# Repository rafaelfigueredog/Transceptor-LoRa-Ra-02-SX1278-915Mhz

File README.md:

# Transceptor-LoRa-Ra-02-SX1278-915Mhz

Este projeto visa a criação de um Transceptor-LoRa-Ra-02-SX1278-915Mhz destinado a disciplina de Técnicas de Prototipagem do curso de Engenharia de Computação no Instituto Federal da Paraíba

## Grupo

  Allan Bispo <br />
  Lucas Mateus <br />
  Rafael Guimarães <br />
  
## Componentes

- Transceptor LoRa Ra-02 SX1278 915Mhz
- Microcontrolador ATmega328
- Bateria de 5v Li-ion

## Aplicação - Monitoramento de Animais. 

Esse projeto visa a criação de um dispositivo que emite sinais de radio frequencia, de modo que seja possível estimar a distância entre o animal e um ponto específico determinado pelo usuário do projeto auxiliando o dono a localizar o animal.

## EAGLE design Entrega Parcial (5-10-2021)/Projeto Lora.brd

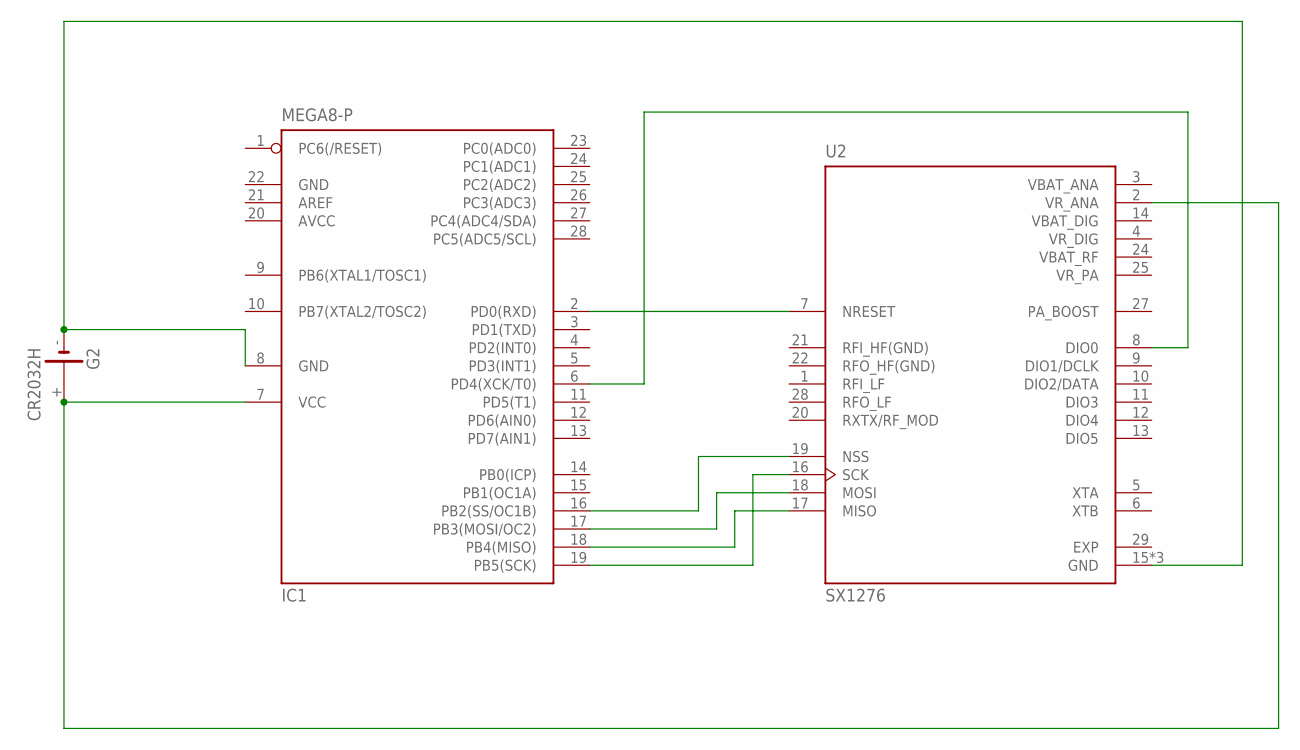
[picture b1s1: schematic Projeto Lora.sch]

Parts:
G2: CR2032H
IC1: MEGA8-P; DIL28-3
U2: SX1276; QFN65P600X600X100-29N

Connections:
AVCC: IC1.20 (AVCC)
EXP: U2.29 (EXP)
GND: IC1.22 (GND)
unnamed: IC1.18 (PB4(MISO)), U2.17 (MISO)
unnamed: IC1.17 (PB3(MOSI/OC2)), U2.18 (MOSI)
unnamed: IC1.16 (PB2(SS/OC1B)), U2.19 (NSS)
unnamed: IC1.19 (PB5(SCK)), U2.16 (SCK)
unnamed: G2.+, IC1.7 (VCC), U2.2 (VR_ANA)
unnamed: IC1.2 (PD0(RXD)), U2.7 (NRESET)
unnamed: G2.-, IC1.8 (GND), U2.15 (GND), U2.23 (GND), U2.26 (GND)
unnamed: IC1.6 (PD4(XCK/T0)), U2.8 (DIO0)
VBAT_ANA: U2.3 (VBAT_ANA)
VBAT_DIG: U2.14 (VBAT_DIG)
VBAT_RF: U2.24 (VBAT_RF)
VR_DIG: U2.4 (VR_DIG)
VR_PA: U2.25 (VR_PA)

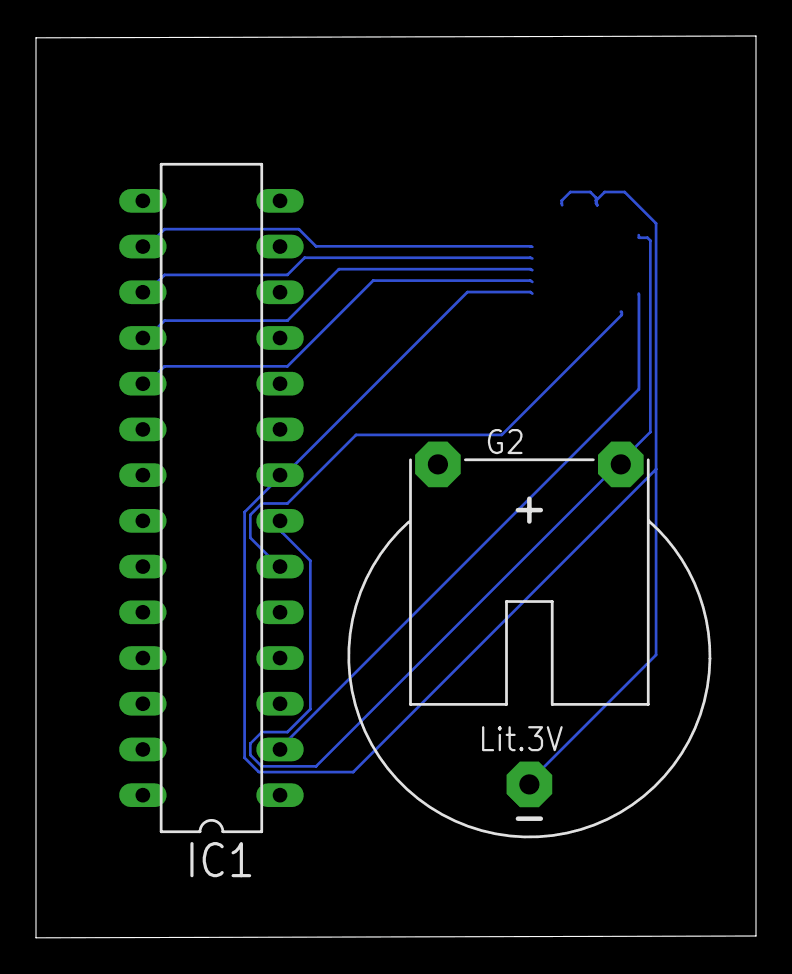
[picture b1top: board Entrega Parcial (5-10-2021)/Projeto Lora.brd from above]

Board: 2 copper layers, 40.0 x 50.1 mm, 3 parts (1 on the bottom side), 8 nets.

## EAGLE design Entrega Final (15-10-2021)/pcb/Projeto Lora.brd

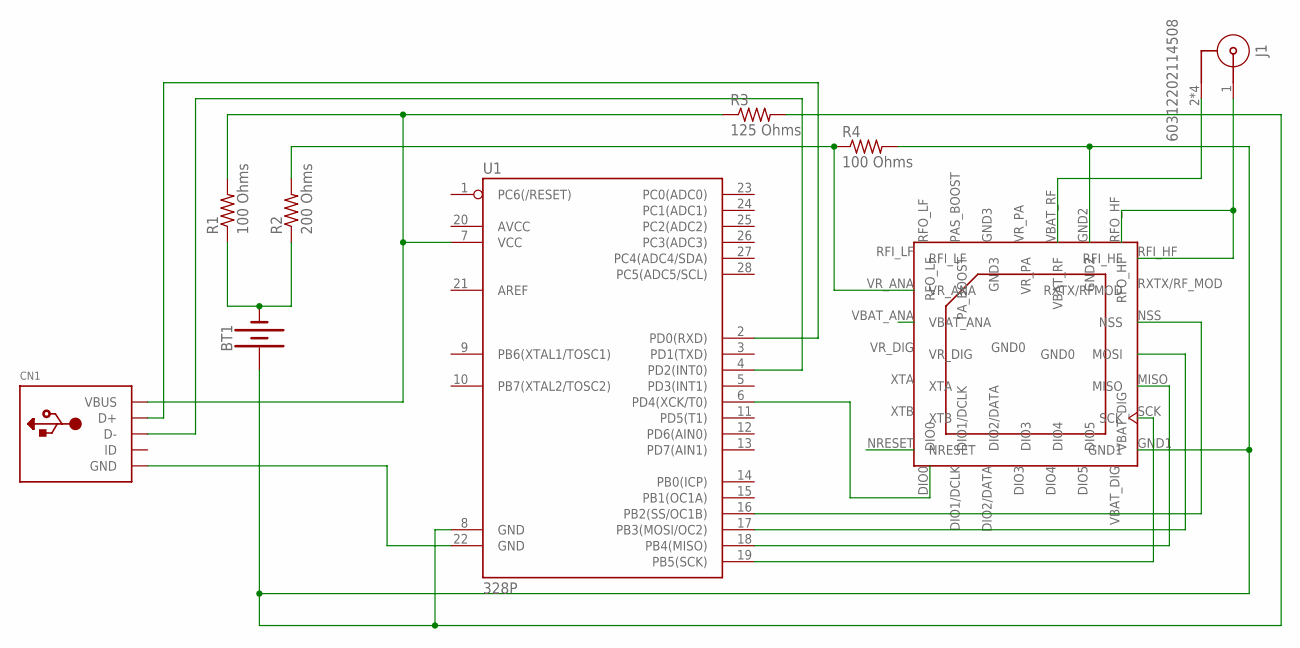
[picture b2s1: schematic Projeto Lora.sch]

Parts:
BT1: BATTERY-9V; BATTCON_9V
CN1: USBMINIB; USB-MINIB
J1: 60312202114508
R1, R4: 100 Ohms; R01005
R2: 200 Ohms; R01005
R3: 125 Ohms; R01005
U1: 328P; DIP28
U$1: LORA-SX1278; PDIP

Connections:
GND0: U$1.GND0
GND3: U$1.GND3
unnamed: U1.6 (PD4(XCK/T0)), U$1.DIO0
unnamed: U1.19 (PB5(SCK)), U$1.SCK
unnamed: U1.18 (PB4(MISO)), U$1.MISO
unnamed: U1.17 (PB3(MOSI/OC2)), U$1.MOSI
unnamed: U1.16 (PB2(SS/OC1B)), U$1.NSS
unnamed: J1.1, U$1.RFI_HF, U$1.RFO_HF
unnamed: CN1.VBUS, R1.2, R3.1, U1.7 (VCC)
unnamed: R2.2, R4.1, U$1.VR_ANA
unnamed: J1.2, J1.3 (2), J1.4 (2), J1.5 (2), U$1.VBAT_RF
unnamed: BT1.-, R1.1, R2.1
unnamed: BT1.+, R3.2, R4.2, U1.8 (GND), U$1.GND1, U$1.GND2
unnamed: CN1.GND, U1.22 (GND)
unnamed: CN1.D+, U1.2 (PD0(RXD))
unnamed: CN1.D-, U1.4 (PD2(INT0))
VBAT_DIG: U$1.VBAT_DIG
VR_DIG: U$1.VR_DIG
VR_PA: U$1.VR_PA

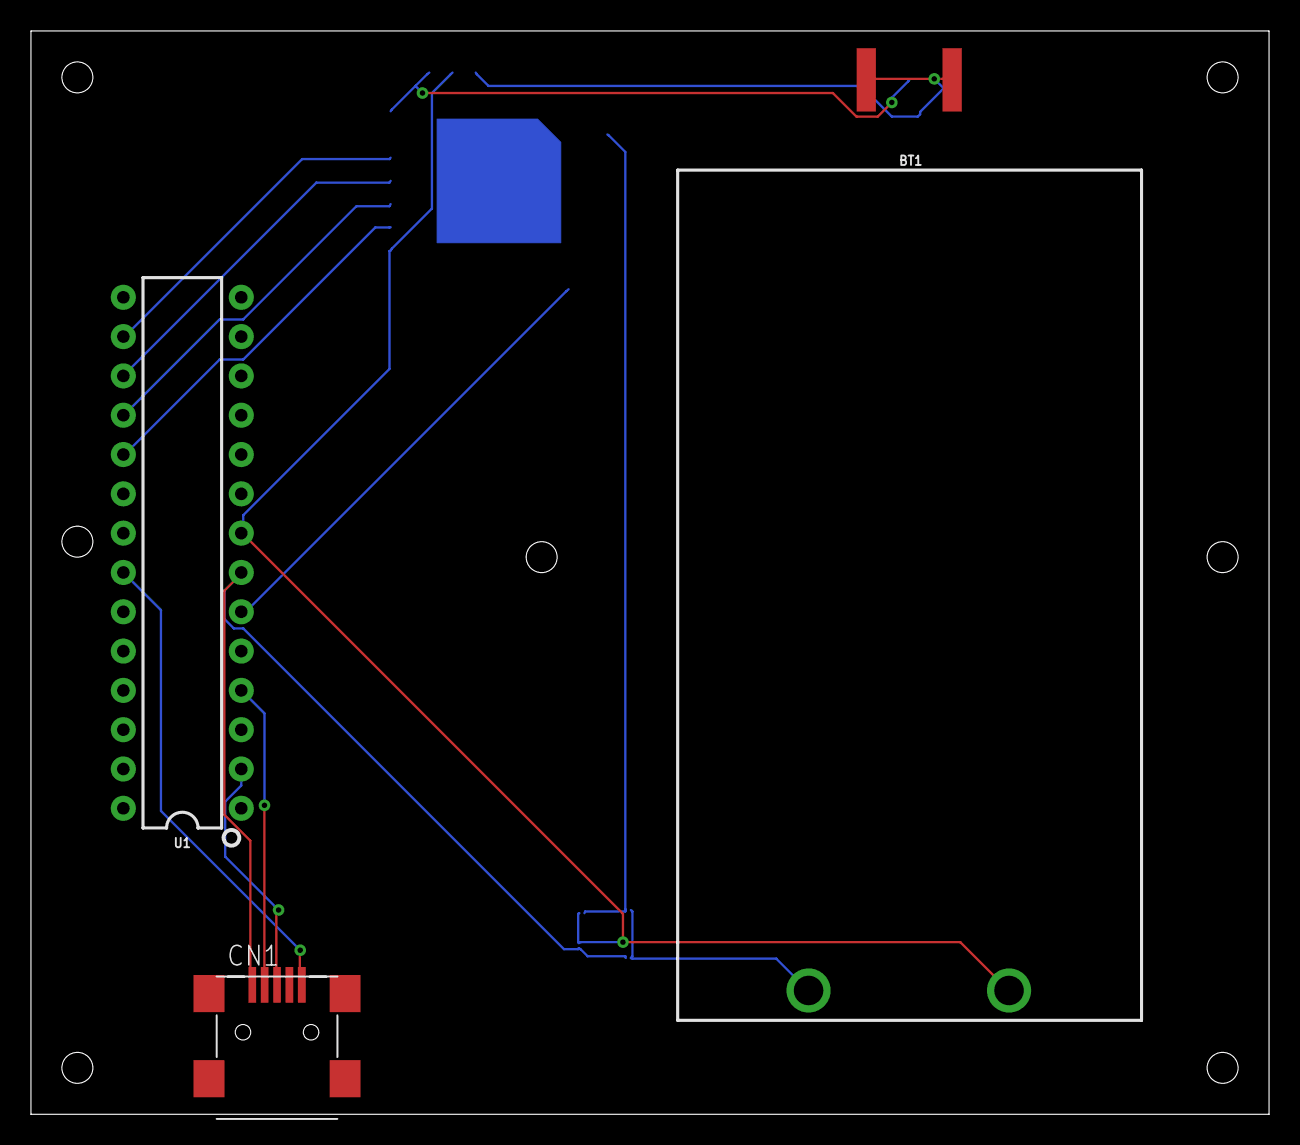
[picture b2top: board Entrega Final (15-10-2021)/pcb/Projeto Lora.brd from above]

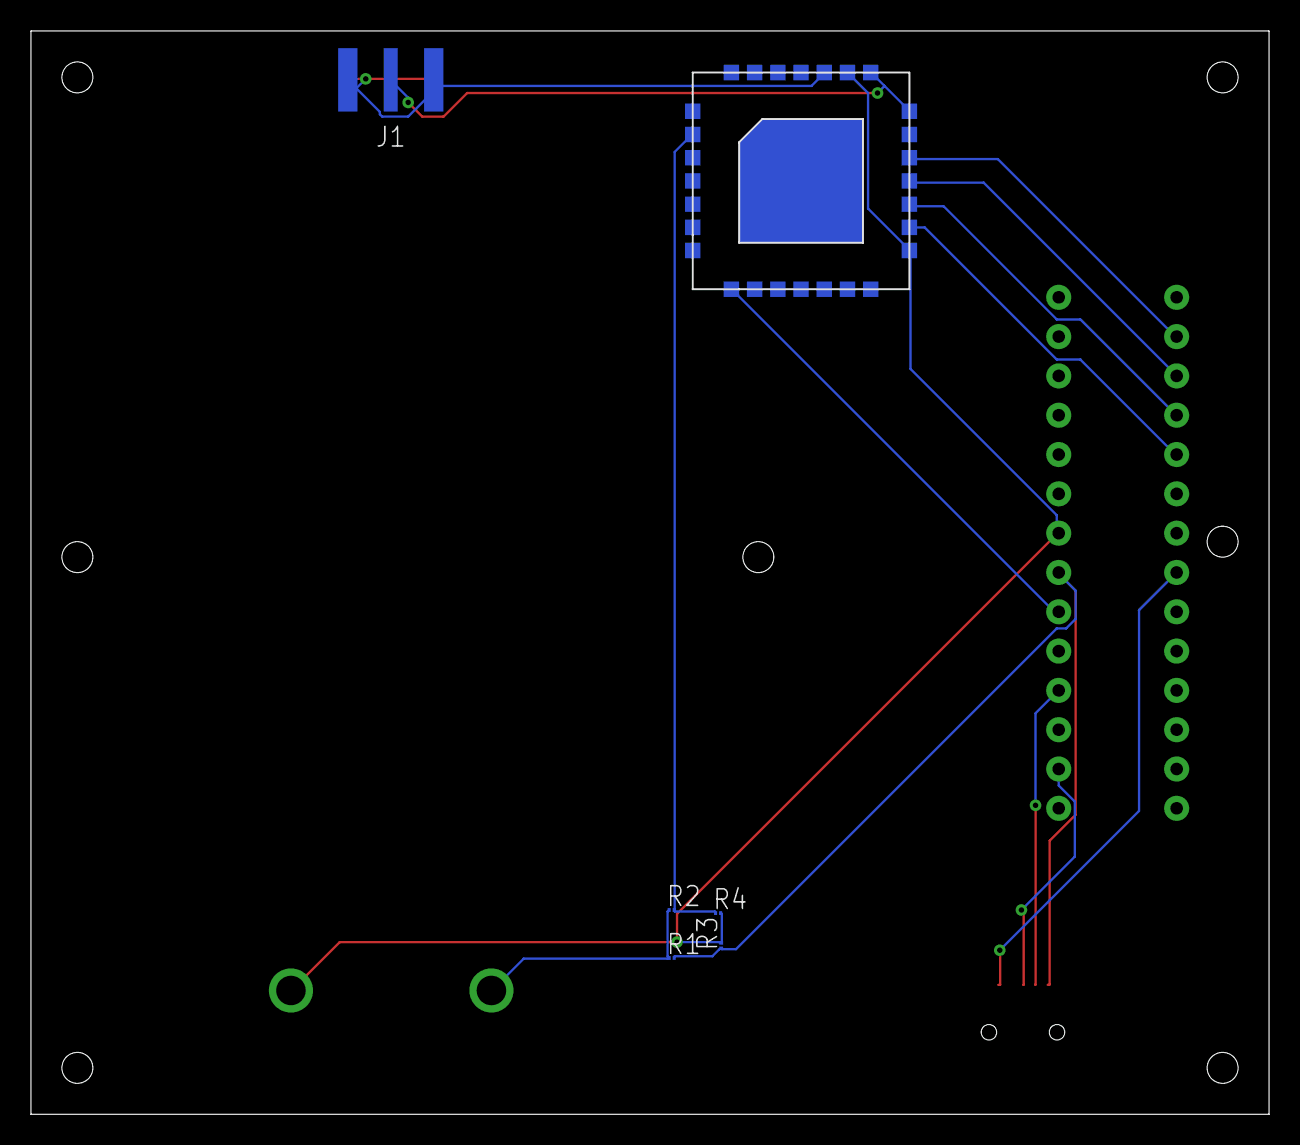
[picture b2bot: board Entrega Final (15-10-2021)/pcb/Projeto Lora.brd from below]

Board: 2 copper layers, 80.0 x 70.0 mm, 9 parts (6 on the bottom side), 14 nets.

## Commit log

2021-07-30 Add docs/datasheets and update readme
2021-07-30 deleted files
2021-08-06 Add Application
2021-09-10 #Add PCB Files
2021-10-15 Update: Add case for update schema pcb and 3d files
2021-10-15 stl and gcode files added

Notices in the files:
parts and their libraries:
SparkFun-IC-Microcontroller: Licensing: Creative Commons ShareAlike 4.0 International - https://creativecommons.org/licenses/by-sa/4.0
